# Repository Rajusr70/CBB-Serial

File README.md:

CBB-Serial
==========

This repository contains the design files for the Logic Supply CBB-Serial Cape for the 
BeagleBone and BeagleBone Black. It adds RS232, RS485 and CAN communication capabilities
to the BeagleBone.

The CBB-Serial Cape is available at http://www.logicsupply.com/components/beaglebone/capes/cbb-serial/

Check out the CBB-Serial manual at https://docs.google.com/document/d/1y0aKYqKd3_5HuzUvIepQmC5AjbFIqBlBak-Jtv0YB7Q/edit?usp=sharing

----

Follow us on Google+ for updates and more information: https://plus.google.com/u/0/b/103613886667848850929/

Created by Alexander Hiam for Logic Supply.

This work is licensed under the Creative Commons Attribution-Share Alike 3.0 Unported License. 
To view a copy of this license, visit http://creativecommons.org/licenses/by-sa/3.0/ or send a 
letter to Creative Commons, 171 Second Street, Suite 300, San Francisco, California, 94105, USA.

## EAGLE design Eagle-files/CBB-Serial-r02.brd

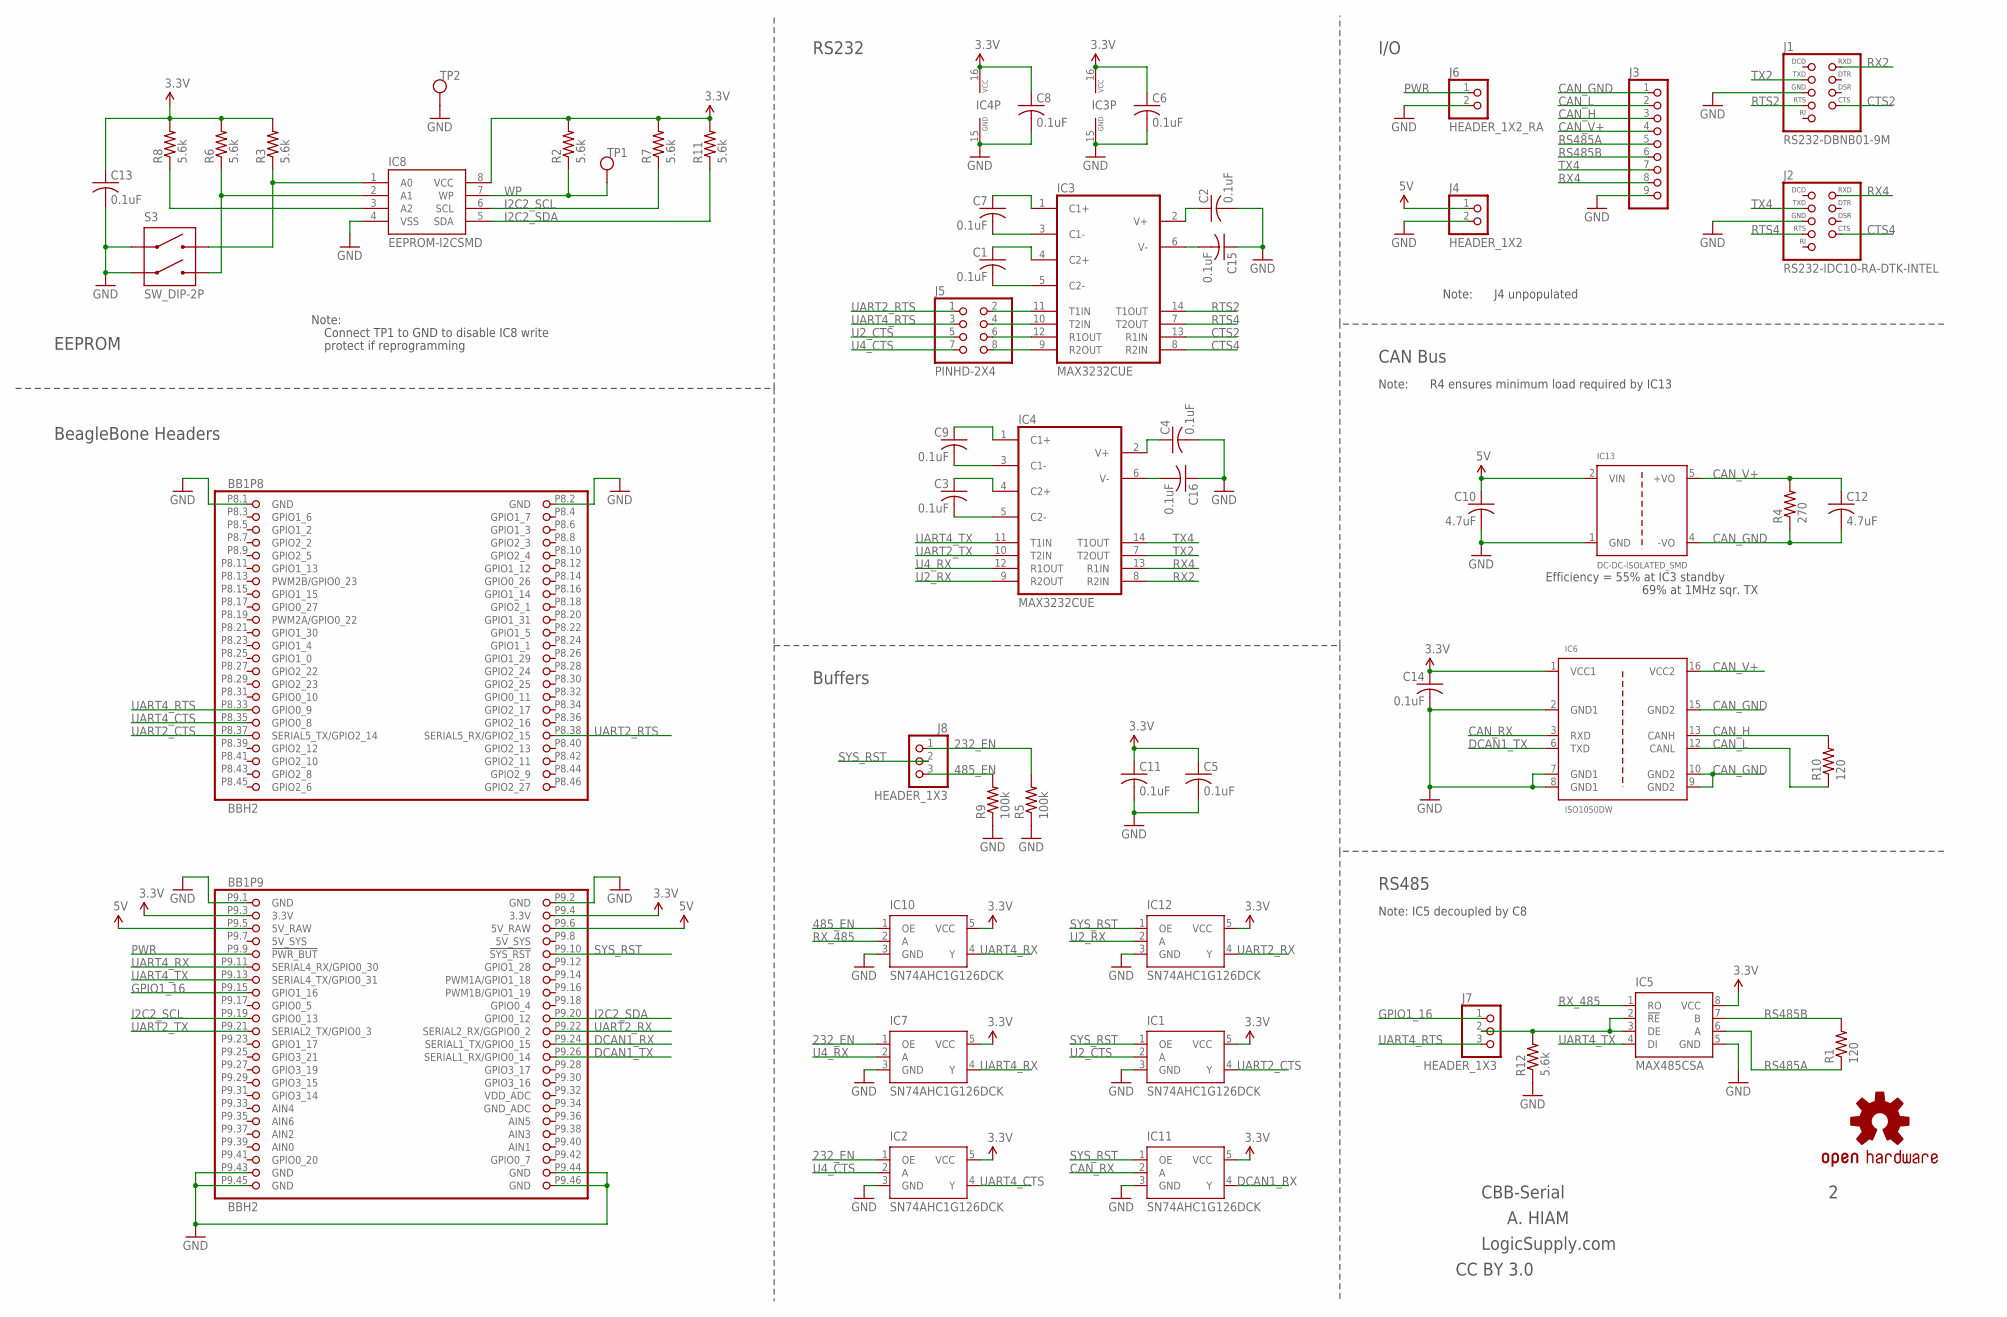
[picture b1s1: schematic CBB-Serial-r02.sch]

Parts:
BB1: BBH2; BB_CAPE_TOP
C1, C2, C3, C4, C5, C6, C7, C8, C9, C11, C13, C14, C15, C16: 0.1uF; C0603
C10, C12: 4.7uF; C0805
IC1, IC2, IC7, IC10, IC11, IC12: SN74AHC1G126DCK; DCK-R-PDSO-G5
IC3, IC4: MAX3232CUE; TSSOP16; MPN MAX3232CUE+
IC5: MAX485CSA; SO08
IC6: ISO1050DW; SO16W
IC8: EEPROM-I2CSMD; SO08
IC13: DC-DC-ISOLATED_SMD; DC-DC-SMD
J1: RS232-DBNB01-9M; DB9-DBNB01-9M
J2: RS232-IDC10-RA-DTK-INTEL; HEADER_2X5-SHROUDED-RA
J3: SCREWTERM_9PIN_2-54; SCREWTERM_1725724_9
J4: HEADER_1X2
J5: PINHD-2X4; HEADER_2X4
J6: HEADER_1X2_RA
J7, J8: HEADER_1X3
R1, R10: 120; R1206
R2, R3, R6, R7, R8, R11, R12: 5.6k; R0603
R4: 270; R1206
R5, R9: 100k; R0603
S3: SW_DIP-2P; DIPSWITCH-2P-SMD-1.27
TP1, TP2: TEST_POINT_PTH
U$7: OSHW-LOGOM; OSHW-LOGO-M

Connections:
3.3V: BB1.P9.3 (3.3V), BB1.P9.4 (3.3V), C5.1, C6.1, C8.1, C11.1, C13.1, C14.1, IC1.5 (VCC), IC2.5 (VCC), IC3.16 (VCC), IC4.16 (VCC), IC5.8 (VCC), IC6.1 (VCC1), IC7.5 (VCC), IC8.8 (VCC), IC10.5 (VCC), IC11.5 (VCC), IC12.5 (VCC), R2.2, R3.2, R6.2, R7.2, R8.2, R11.2
5V: BB1.P9.5 (5V_RAW), BB1.P9.6 (5V_RAW), C10.1, IC13.2 (VIN), J4.1
5V_SYS: BB1.P9.7 (5V_SYS), BB1.P9.8 (5V_SYS)
232_EN: IC2.1 (OE), IC7.1 (OE), J8.1, R5.2
485_EN: IC10.1 (OE), J8.3, R9.2
CAN_GND: C12.2, IC6.9 (GND2), IC6.10 (GND2), IC6.15 (GND2), IC13.4 (-VO), J3.1, R4.1
CAN_H: IC6.13 (CANH), J3.3, R10.2
CAN_L: IC6.12 (CANL), J3.2, R10.1
CAN_RX: IC6.3 (RXD), IC11.2 (A)
CAN_V+: C12.1, IC6.16 (VCC2), IC13.5 (+VO), J3.4, R4.2
CTS2: IC3.13 (R1IN), J1.8 (CTS)
CTS4: IC3.8 (R2IN), J2.6 (CTS)
DCAN1_RX: BB1.P9.24 (SERIAL1_TX/GPIO0_15), IC11.4 (Y)
DCAN1_TX: BB1.P9.26 (SERIAL1_RX/GPIO0_14), IC6.6 (TXD)
GND: BB1.P8.1 (GND), BB1.P8.2 (GND), BB1.P9.1 (GND), BB1.P9.2 (GND), BB1.P9.43 (GND), BB1.P9.44 (GND), BB1.P9.45 (GND), BB1.P9.46 (GND), C2.2, C4.2, C5.2, C6.2, C8.2, C10.2, C11.2, C13.2, C14.2, C15.1, C16.1, IC1.3 (GND), IC2.3 (GND), IC3.15 (GND), IC4.15 (GND), IC5.5 (GND), IC6.2 (GND1), IC6.7 (GND1), IC6.8 (GND1), IC7.3 (GND), IC8.4 (VSS), IC10.3 (GND), IC11.3 (GND), IC12.3 (GND), IC13.1 (GND), J1.5 (GND), J2.9 (GND), J3.9, J4.2, J6.2, R5.1, R9.1, R12.1, S3.1A, S3.2A, TP2.P$1
GPIO1_16: BB1.P9.15 (GPIO1_16), J7.1
I2C2_SCL: BB1.P9.19 (GPIO0_13), IC8.6 (SCL), R7.1
I2C2_SDA: BB1.P9.20 (GPIO0_12), IC8.5 (SDA), R11.1
unnamed: C9.2, IC4.3 (C1-)
unnamed: C3.2, IC4.5 (C2-)
unnamed: C9.1, IC4.1 (C1+)
unnamed: C3.1, IC4.4 (C2+)
unnamed: C16.2, IC4.6 (V-)
unnamed: C4.1, IC4.2 (V+)
unnamed: C15.2, IC3.6 (V-)
unnamed: C7.2, IC3.3 (C1-)
unnamed: IC5.2 (!RE), IC5.3 (DE), J7.2, R12.2
unnamed: C1.2, IC3.5 (C2-)
unnamed: C7.1, IC3.1 (C1+)
unnamed: C1.1, IC3.4 (C2+)
unnamed: IC8.1 (A0), R3.1, S3.1B
unnamed: IC8.2 (A1), R6.1, S3.2B
unnamed: IC8.3 (A2), R8.1
unnamed: C2.1, IC3.2 (V+)
unnamed: IC3.11 (T1IN), J5.2
unnamed: IC3.12 (R1OUT), J5.6
unnamed: IC3.10 (T2IN), J5.4
unnamed: IC3.9 (R2OUT), J5.8
PWR: BB1.P9.9 (!PWR_BUT), J6.1
RS485A: IC5.6 (A), J3.5, R1.1
RS485B: IC5.7 (B), J3.6, R1.2
RTS2: IC3.14 (T1OUT), J1.7 (RTS)
RTS4: IC3.7 (T2OUT), J2.4 (RTS)
RX2: IC4.8 (R2IN), J1.2 (RXD)
RX4: IC4.13 (R1IN), J2.3 (RXD), J3.8
RX_485: IC5.1 (RO), IC10.2 (A)
SYS_RST: BB1.P9.10 (!SYS_RST), IC1.1 (OE), IC11.1 (OE), IC12.1 (OE), J8.2
TX2: IC4.7 (T2OUT), J1.3 (TXD)
TX4: IC4.14 (T1OUT), J2.5 (TXD), J3.7
U2_CTS: IC1.2 (A), J5.5
U2_RX: IC4.9 (R2OUT), IC12.2 (A)
U4_CTS: IC2.2 (A), J5.7
U4_RX: IC4.12 (R1OUT), IC7.2 (A)
UART2_CTS: BB1.P8.37 (SERIAL5_TX/GPIO2_14), IC1.4 (Y)
UART2_RTS: BB1.P8.38 (SERIAL5_RX/GPIO2_15), J5.1
UART2_RX: BB1.P9.22 (SERIAL2_RX/GGPIO0_2), IC12.4 (Y)
UART2_TX: BB1.P9.21 (SERIAL2_TX/GPIO0_3), IC4.10 (T2IN)
UART4_CTS: BB1.P8.35 (GPIO0_8), IC2.4 (Y)
UART4_RTS: BB1.P8.33 (GPIO0_9), J5.3, J7.3
UART4_RX: BB1.P9.11 (SERIAL4_RX/GPIO0_30), IC7.4 (Y), IC10.4 (Y)
UART4_TX: BB1.P9.13 (SERIAL4_TX/GPIO0_31), IC4.11 (T1IN), IC5.4 (DI)
WP: IC8.7 (WP), R2.1, TP1.P$1

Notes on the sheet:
CBB-Serial
A. HIAM
EEPROM
BeagleBone Headers
RS485
I/O
CAN Bus
RS232
LogicSupply.com
R4 ensures minimum load required by IC13
Efficiency = 55% at IC3 standby
69% at 1MHz sqr. TX
Buffers
Note: IC5 decoupled by C8
Note:
Connect TP1 to GND to disable IC8 write
protect if reprogramming
J4 unpopulated
CC BY 3.0

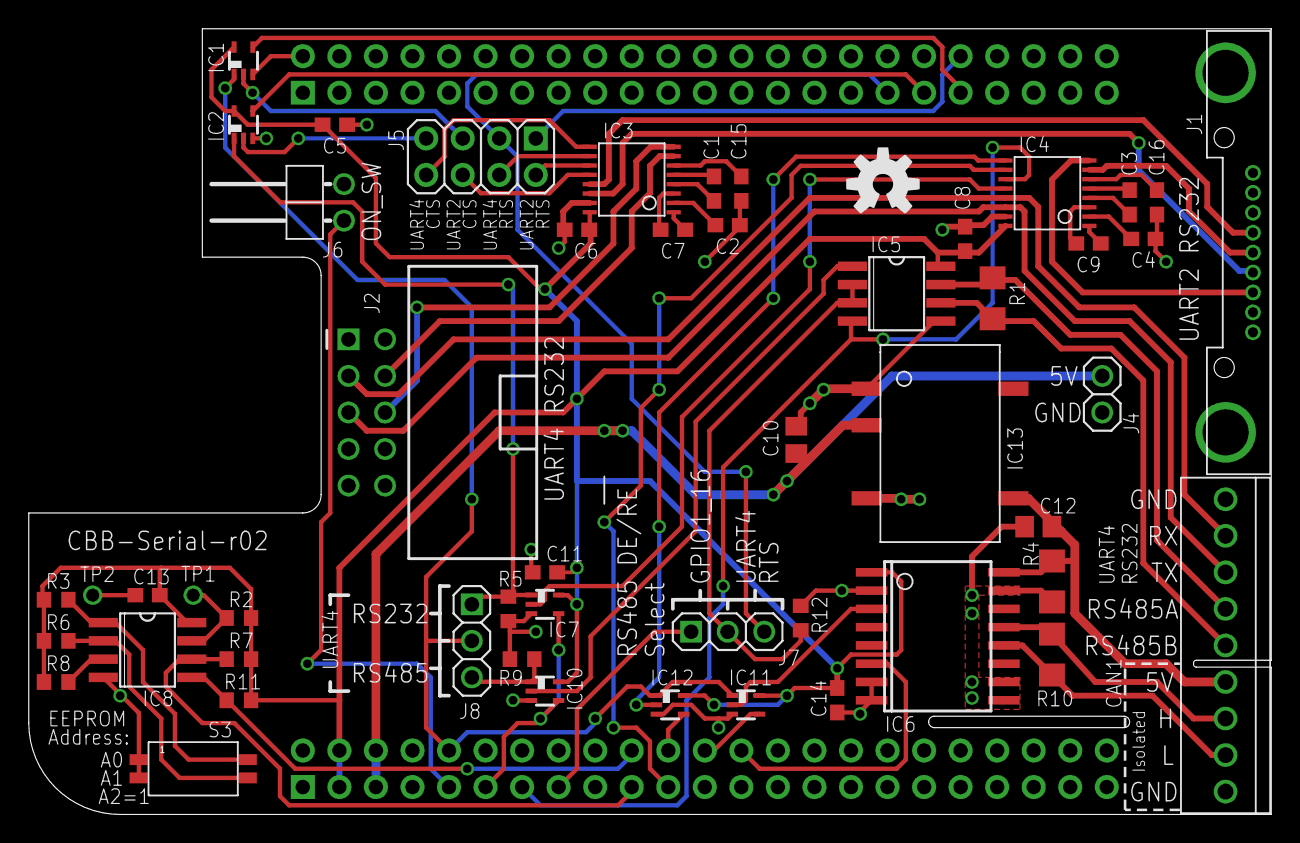
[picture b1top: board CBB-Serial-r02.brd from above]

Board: 2 copper layers, 86.4 x 54.6 mm, 53 parts (1 on the bottom side), 62 nets.

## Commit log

2014-01-23 added README and schematic
2014-01-23 update to r02 schematic
2014-01-23 added link to manual
2014-06-03 added Eagle files
2014-06-03 link to product page
2014-06-11 added overlays
2014-07-15 added SketchUp model

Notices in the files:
parts and their libraries:
SparkFun-Aesthetics: Licensing: CC v3.0 Share-Alike You are welcome to use this library for commercial purposes.
